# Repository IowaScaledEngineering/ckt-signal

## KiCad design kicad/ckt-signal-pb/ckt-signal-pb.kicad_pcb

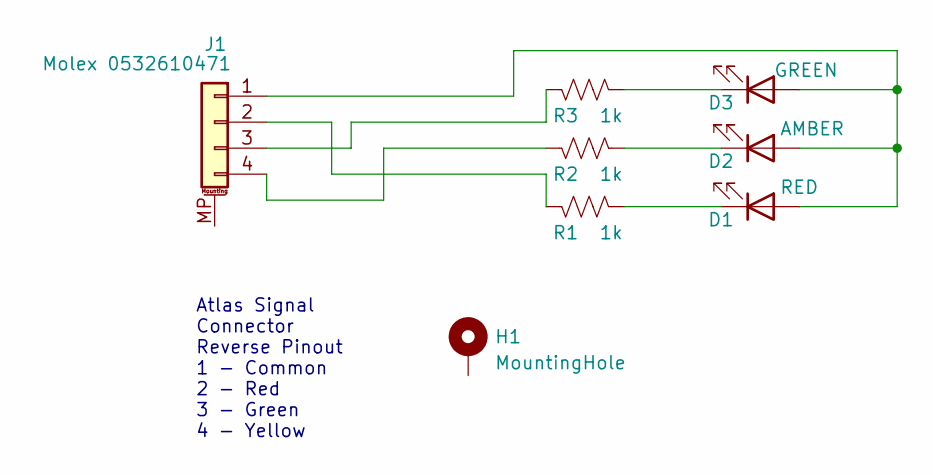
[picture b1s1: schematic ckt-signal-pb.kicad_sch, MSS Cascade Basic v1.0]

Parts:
D1: RED; LED_0805_2012Metric
D2: AMBER; LED_0805_2012Metric
D3: GREEN; LED_0805_2012Metric
H1: MountingHole; MountingHole_3.2mm_M3_Pad
J1: Molex 0532610471; Molex_PicoBlade_53261-0471_1x04-1MP_P1.25mm_Horizontal
R1, R2, R3: 1k; R_0805_2012Metric

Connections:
unnamed: D1.1 (K), R1.1
unnamed: D1.2 (A), D2.2 (A), D3.2 (A), J1.1
unnamed: D2.1 (K), R2.1
unnamed: D3.1 (K), R3.1
unnamed: J1.2, R1.2
unnamed: J1.3, R3.2
unnamed: J1.4, R2.2

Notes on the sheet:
Atlas Signal Connector Reverse Pinout 1 - Common 2 - Red 3 - Green 4 - Yellow

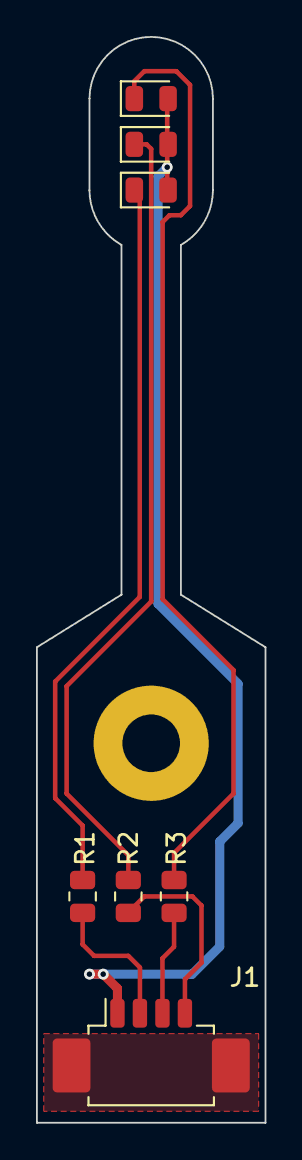
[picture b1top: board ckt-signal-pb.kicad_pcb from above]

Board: 2 copper layers, 12.7 x 60.3 mm, 8 parts (0 on the bottom side), 7 nets.

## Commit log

2013-12-27 Initial Checkin
2013-12-30 Added version #
2013-12-30 Added outline layer
2014-01-11 PG files
2015-10-08 New vertical version
2015-10-12 Add start of PCB signal bases
2015-10-12 Add signal base pcb for 1x
2015-10-12 Updated layouts for 1x and 2x bases
2015-10-17 Send to OSH 10/12
2015-11-02 Added manual
2015-11-02 Updated instructions
2015-11-12 Add license and gitignore
2015-12-31 Connect that last pin, just in case
2017-06-01 Reversed R&G to match railroad signal convention, rather than traffic light convention
2017-06-17 Updated to new resistor values
2017-06-17 Added bag topper
2020-09-28 Add signal repeater (with built-in inverter) and signal connector (no inverter)
2020-09-29 Add panelized sigcon boards
2020-10-14 Add ckt-sigcon-panel-6x v1.0
2024-06-08 Add a new temporary signal design
2024-06-08 Fix outline issue
2024-06-08 Panelize the single head signal
2024-06-08 Add version text to single head signal
2024-06-08 Add 2-headed signal
2024-06-08 Repanelize the 1x signals
2024-07-01 2x array
2024-07-01 Fixed Nathan's dangling traces
2024-07-09 Sent to fab July 2024
2025-08-10 Add a reverse picoblade version of the fake signal
2025-08-10 Add 2 head picoblade connector signal
2025-08-19 Rename to match directory name
2025-08-19 Fix up some dangling trace bits that caused DRC to fail
2025-08-19 Add array of ckt-signal-pb
2025-08-19 Cleanup pcb, rename preference file
2025-08-19 Panelize the 2-headed signals
2025-08-20 Redesign 2x signal for better panelization
